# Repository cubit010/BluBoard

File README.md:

<h1 align="center">Bluboard</h1>

An nRF52840 dev board made to be embedded in a custom mechanical keyboard, with as many pins broken out as possible within JLCPCB's 6-layer specs.

---

## What is this?

BluBoard is a custom nRF52840 development board built for use inside a mechanical keyboard. The main goal was to break out as many GPIO pins as possible and also having proper RF capabilities 
most off-the-shelf options such as the nice nano is powerful, but comes at high cost while having low gpio count, this board tries to fix that.

---

## Form Factor

Slightly wider than a Raspberry Pi Pico. Uses two 1×20 pin headers, plus an extra two 1×3 headers near the usb c port for the pins that didn't fit in the main rows.

---

## Features

- **nRF52840** - ARM Cortex-M4F, BLE 5.x, 1MB flash, 256KB RAM
- **USB-C** - power and programming
- **BLE 5.x** - wireless support built in with trace antenna
- **SWD debug header** - for debugging
- **I2C** - broken out, available on most pins
- **SPI** - broken out, available on most pins
- **Analog IO** - most analog pins are broken out, on top or bottom layer with 1oz copper for signal
- **6-layer PCB** - JLCPCB, ENIG finish, filled via for bga
- **Built-in power management** - built in battery support through a jst-ph connector and a BQ24075 charger

---

## Pin Breakout

Power, ground, and GPIO are spread across both 1×20 headers. The extra 1×3 headers cover the remaining pins and utils such as swd.

> Full pinout table coming soon. Check the KiCad schematic in the meantime.

---

## Firmware

BluBoard targets **ZMK**, which has native nRF52840 support and works well for wireless keyboards. Bare metal / Nordic SDK also works if you need it.

> A ZMK shield definition for BluBoard is planned but not yet published.

---

## Why 6 layers?

Jlc's manufacturing options allow for cheap manufacturing of 6 layer boards, in addition, at this form factor, their 6 layer boards are cheaper than 4 layer, while having additional benefits such as enig finish, and free filled vias, so the bga solder points would not be a possible point of failure

---

## Previews
### Schematic

(don't ask why I did this)

### PCB
#### All

#### Top

#### In.1

#### In.2

#### In.3

#### In.4

#### Bottom

*Built with KiCad 9 and 10 · Fabricated via JLCPCB · Part of Hack Club [Blueprint](blueprint.hackclub.com) and [Stasis](stasis.hackclub.com)*

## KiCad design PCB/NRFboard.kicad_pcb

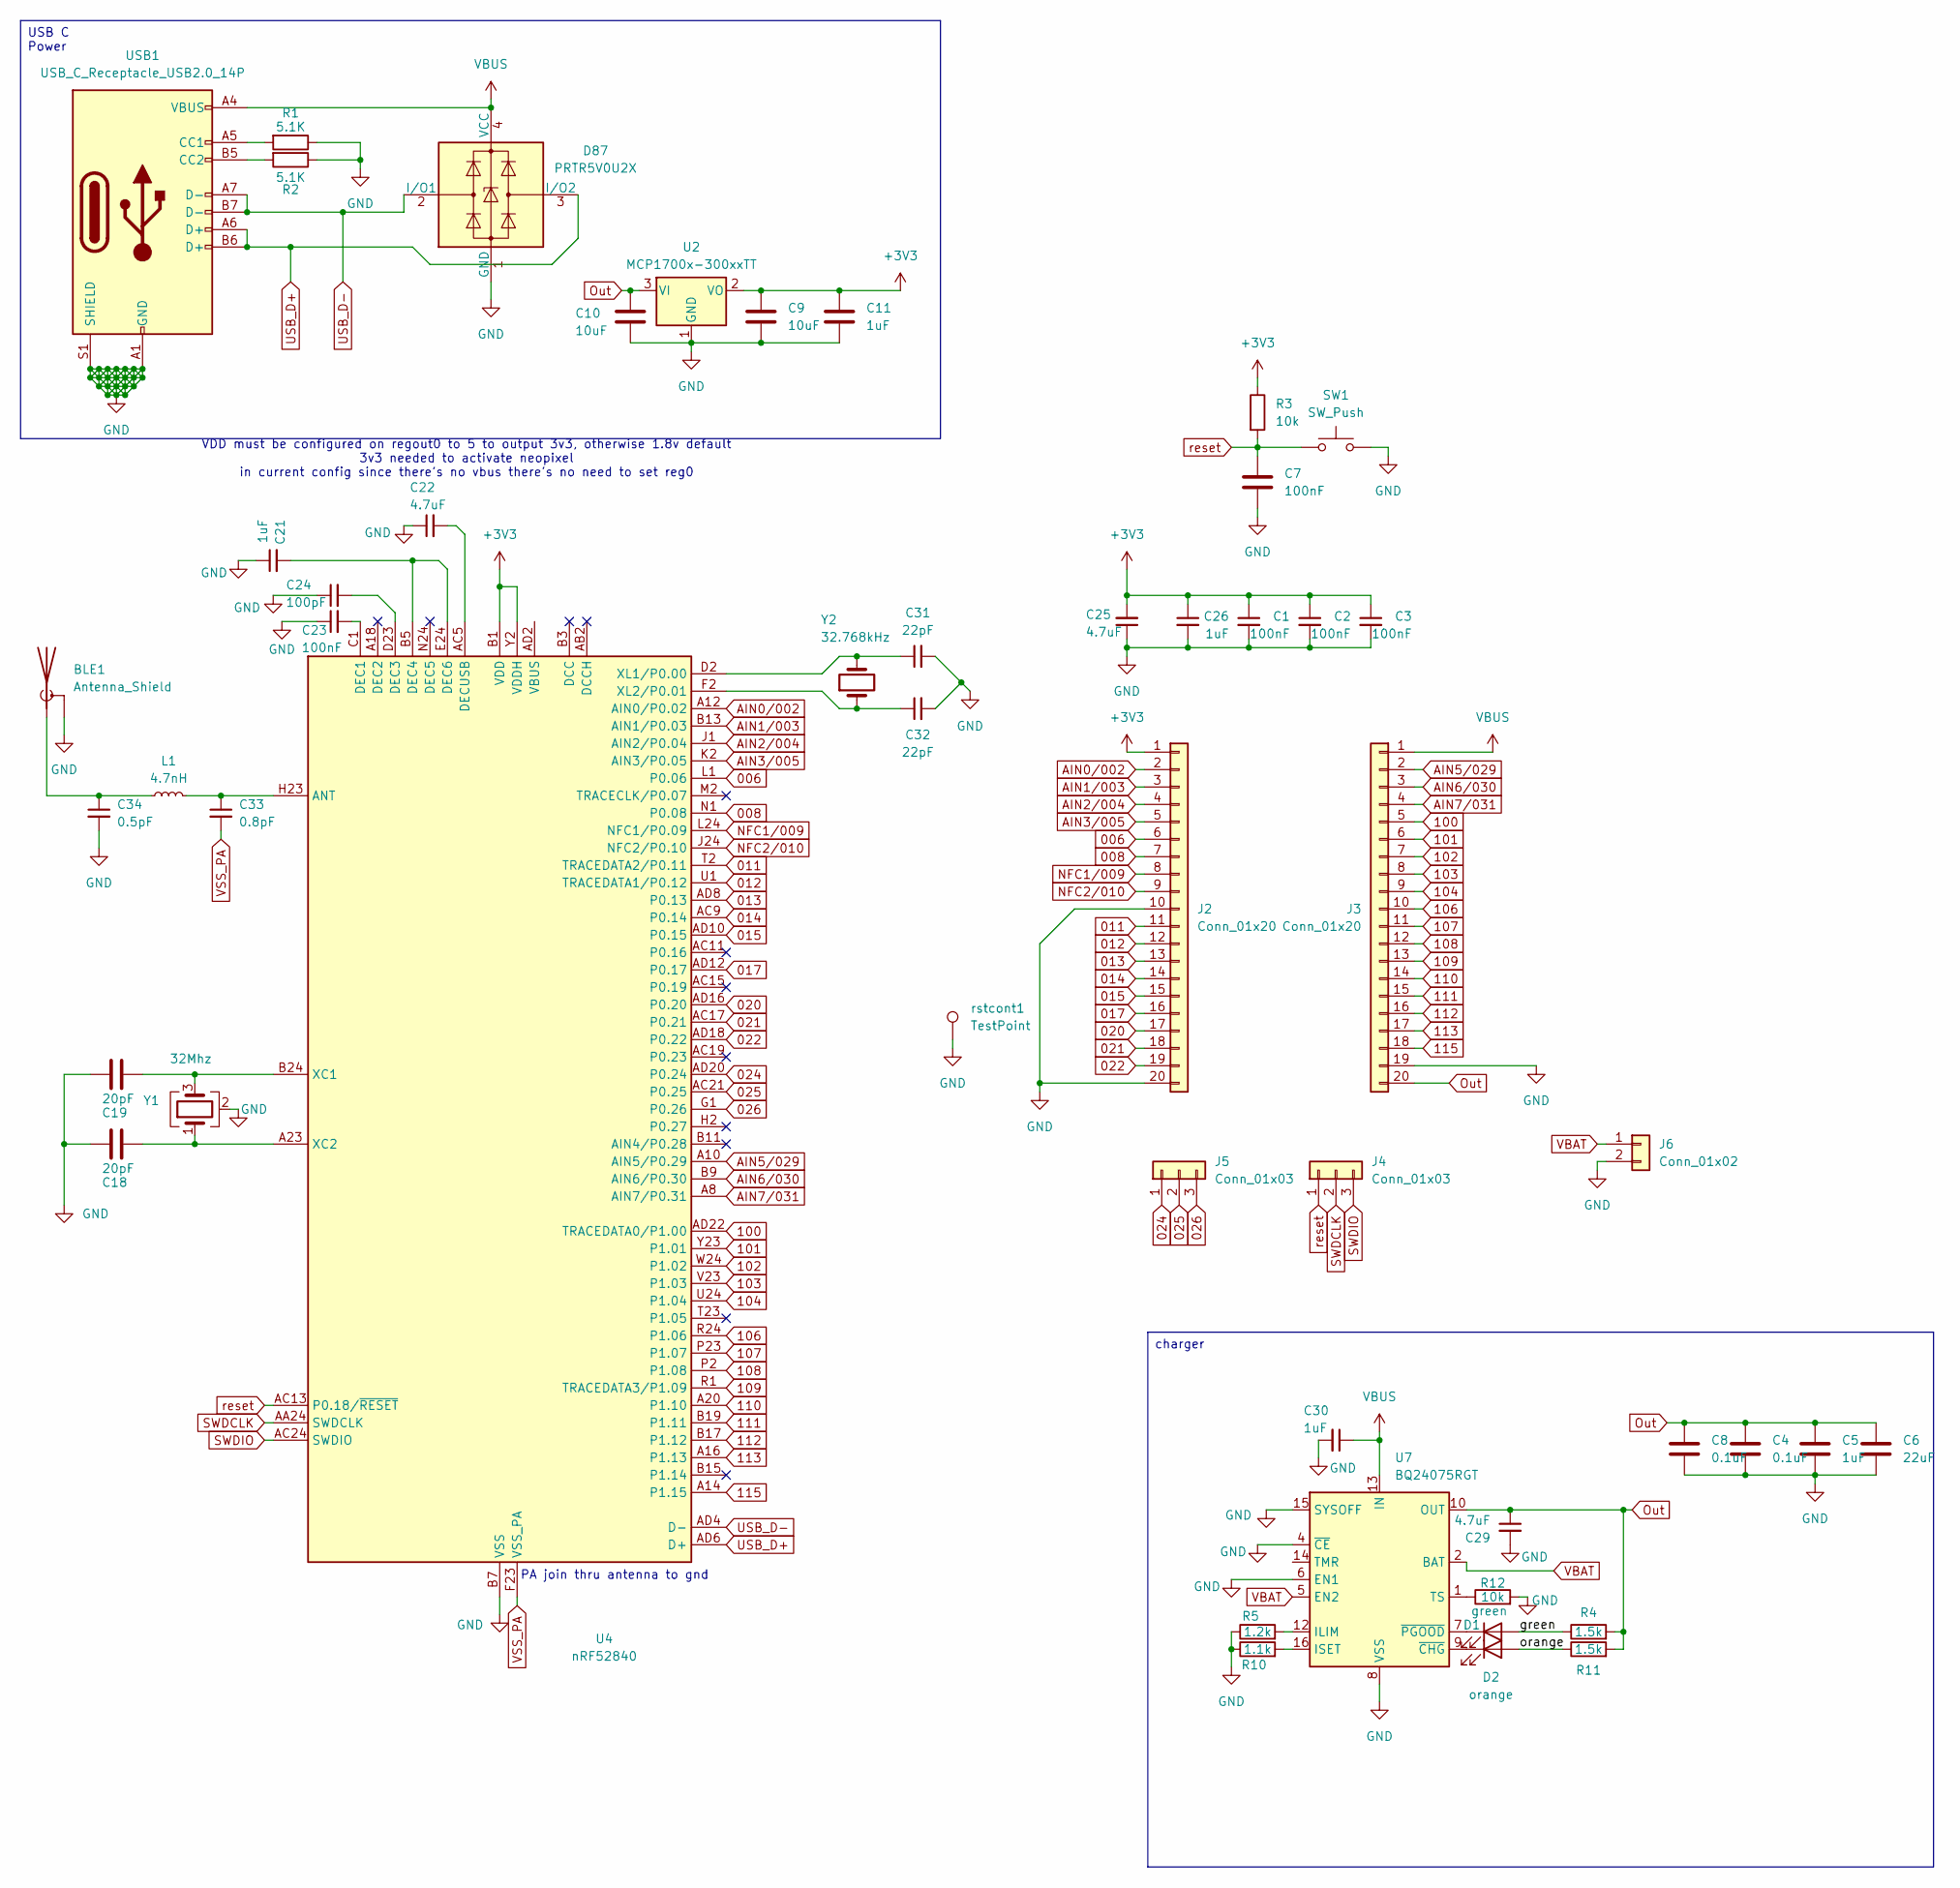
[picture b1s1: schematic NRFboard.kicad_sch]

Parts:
BLE1: Antenna_Shield; Texas_SWRA117D_2.4GHz_Right
C1, C2, C3, C7, C23: 100nF; C_0402_1005Metric
C4, C8: 0.1uF; C_0402_1005Metric
C5, C11, C21, C26, C30: 1uF; C_0402_1005Metric
C6: 22uF; C_0805_2012Metric
C9, C10: 10uF; C_0603_1608Metric
C18, C19: 20pF; C_0402_1005Metric
C22, C25, C29: 4.7uF; C_0603_1608Metric
C24: 100pF; C_0402_1005Metric
C31, C32: 22pF; C_0402_1005Metric
C33: 0.8pF; C_0402_1005Metric
C34: 0.5pF; C_0402_1005Metric
D1: green; LED_0805_2012Metric
D2: orange; LED_0805_2012Metric
D87: PRTR5V0U2X; SOT-143
J2, J3: Conn_01x20; PinHeader_1x20_P2.54mm_Vertical
J4, J5: Conn_01x03; PinHeader_1x03_P2.54mm_Vertical
J6: Conn_01x02; JST_PH_B2B-PH-K_1x02_P2.00mm_Vertical
L1: 4.7nH; L_0402_1005Metric
R1, R2: 5.1K; R_0402_1005Metric
R3, R12: 10k; R_0402_1005Metric
R4, R11: 1.5k; R_0402_1005Metric
R5: 1.2k; R_0402_1005Metric
R10: 1.1k; R_0402_1005Metric
SW1: SW_Push; SW_Push_SPST_NO_Alps_SKRK
U2: MCP1700x-300xxTT; SOT-23
U4: nRF52840; Nordic_AQFN-73-1EP_7x7mm_P0.5mm
U7: BQ24075RGT; VQFN-16-1EP_3x3mm_P0.5mm_EP1.6x1.6mm
USB1: USB_C_Receptacle_USB2.0_14P; USB_C_Receptacle_HRO_TYPE-C-31-M-12
Y1: 32Mhz; Crystal_SMD_3225-4Pin_3.2x2.5mm
Y2: 32.768kHz; Crystal_SMD_3215-2Pin_3.2x1.5mm
rstcont1: TestPoint; TestPoint_Pad_D1.0mm

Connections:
006: J2.6, U4.L1 (P0.06)
008: J2.7, U4.N1 (P0.08)
011: J2.11, U4.T2 (TRACEDATA2/P0.11)
012: J2.12, U4.U1 (TRACEDATA1/P0.12)
013: J2.13, U4.AD8 (P0.13)
014: J2.14, U4.AC9 (P0.14)
015: J2.15, U4.AD10 (P0.15)
017: J2.16, U4.AD12 (P0.17)
020: J2.17, U4.AD16 (P0.20)
021: J2.18, U4.AC17 (P0.21)
022: J2.19, U4.AD18 (P0.22)
024: J5.1, U4.AD20 (P0.24)
025: J5.2, U4.AC21 (P0.25)
026: J5.3, U4.G1 (P0.26)
100: J3.5, U4.AD22 (TRACEDATA0/P1.00)
101: J3.6, U4.Y23 (P1.01)
102: J3.7, U4.W24 (P1.02)
103: J3.8, U4.V23 (P1.03)
104: J3.9, U4.U24 (P1.04)
106: J3.10, U4.R24 (P1.06)
107: J3.11, U4.P23 (P1.07)
108: J3.12, U4.P2 (P1.08)
109: J3.13, U4.R1 (TRACEDATA3/P1.09)
110: J3.14, U4.A20 (P1.10)
111: J3.15, U4.B19 (P1.11)
112: J3.16, U4.B17 (P1.12)
113: J3.17, U4.A16 (P1.13)
115: J3.18, U4.A14 (P1.15)
+3V3: C1.1, C2.1, C3.1, C9.1, C11.1, C25.2, C26.1, J2.1, R3.1, U2.2 (VO), U4.A22 (VDD), U4.AD14 (VDD), U4.AD23 (VDD), U4.B1 (VDD), U4.W1 (VDD), U4.Y2 (VDDH)
/green: D1.2 (A), R4.1
/orange: D2.2 (A), R11.1
AIN0/002: J2.2, U4.A12 (AIN0/P0.02)
AIN1/003: J2.3, U4.B13 (AIN1/P0.03)
AIN2/004: J2.4, U4.J1 (AIN2/P0.04)
AIN3/005: J2.5, U4.K2 (AIN3/P0.05)
AIN5/029: J3.2, U4.A10 (AIN5/P0.29)
AIN6/030: J3.3, U4.B9 (AIN6/P0.30)
AIN7/031: J3.4, U4.A8 (AIN7/P0.31)
GND: BLE1.2 (Shield), C1.2, C2.2, C3.2, C4.2, C5.2, C6.2, C7.2, C8.2, C9.2, C10.1, C11.2, C18.1, C19.1, C21.1, C22.1, C23.1, C24.1, C25.1, C26.2, C29.2, C30.2, C31.2, C32.2, C34.2, D87.1 (GND), J2.10, J2.20, J3.19, J6.2, R1.1, R2.1, R5.1, R10.1, R12.2, SW1.2, U2.1 (GND), U4.B7 (VSS), U4.EP (VSS), U7.4 (~CE), U7.6 (EN1), U7.8 (VSS), U7.15 (SYSOFF), U7.17 (VSS), USB1.A1 (GND), USB1.A12 (GND), USB1.B1 (GND), USB1.B12 (GND), USB1.S1 (SHIELD), Y1.2 (G), Y1.4 (G), rstcont1.1 (1_1)
NFC1/009: J2.8, U4.L24 (NFC1/P0.09)
NFC2/010: J2.9, U4.J24 (NFC2/P0.10)
unnamed: BLE1.1 (A), C34.1, L1.1
unnamed: D1.1 (K), U7.7 (~PGOOD)
unnamed: D2.1 (K), U7.9 (~CHG)
unnamed: C33.1, L1.2, U4.H23 (ANT)
unnamed: C23.2, U4.C1 (DEC1)
unnamed: C24.2, U4.D23 (DEC3)
unnamed: C21.2, U4.B5 (DEC4), U4.E24 (DEC6)
unnamed: C22.2, U4.AC5 (DECUSB)
unnamed: C19.2, U4.B24 (XC1), Y1.3
unnamed: C18.2, U4.A23 (XC2), Y1.1
unnamed: C31.1, U4.D2 (XL1/P0.00), Y2.2
unnamed: C32.1, U4.F2 (XL2/P0.01), Y2.1
unnamed: R5.2, U7.12 (ILIM)
unnamed: R10.2, U7.16 (ISET)
unnamed: R12.1, U7.1 (TS)
unnamed: R1.2, USB1.A5 (CC1)
unnamed: R2.2, USB1.B5 (CC2)
Out: C4.1, C5.1, C6.1, C8.1, C10.2, C29.1, J3.20, R4.2, R11.2, U2.3 (VI), U7.10 (OUT), U7.11 (OUT)
SWDCLK: J4.2, U4.AA24 (SWDCLK)
SWDIO: J4.3, U4.AC24 (SWDIO)
USB_D+: D87.3 (I/O2), U4.AD6 (D+), USB1.A6 (D+), USB1.B6 (D+)
USB_D-: D87.2 (I/O1), U4.AD4 (D-), USB1.A7 (D-), USB1.B7 (D-)
VBAT: J6.1, U7.2 (BAT), U7.3 (BAT), U7.5 (EN2)
VBUS: C30.1, D87.4 (VCC), J3.1, U7.13 (IN), USB1.A4 (VBUS), USB1.A9 (VBUS), USB1.B4 (VBUS), USB1.B9 (VBUS)
VSS_PA: C33.2, U4.F23 (VSS_PA)
reset: C7.1, J4.1, R3.2, SW1.1, U4.AC13 (P0.18/~RESET)

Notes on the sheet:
VDD must be configured on regout0 to 5 to output 3v3, otherwise 1.8v default 3v3 needed to activate neopixel in current config since there's no vbus there's no need to set reg0
PA join thru antenna to gnd
charger
USB C Power

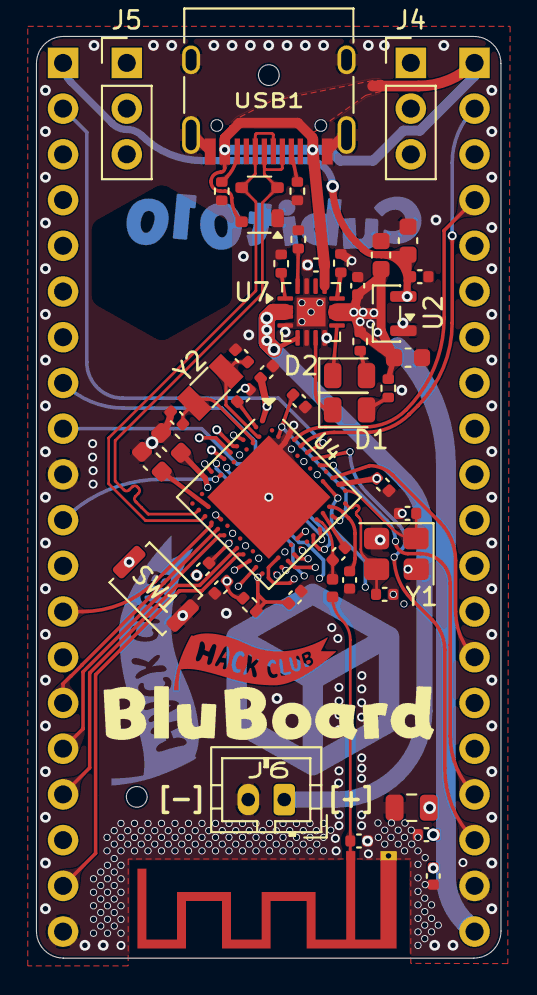
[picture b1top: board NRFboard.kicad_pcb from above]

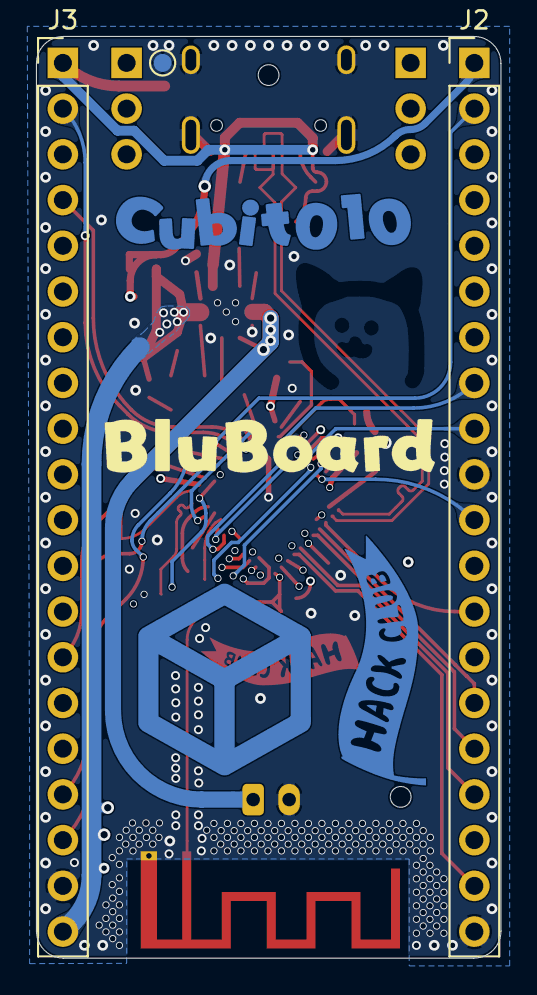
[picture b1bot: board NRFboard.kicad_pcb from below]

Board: 6 copper layers, 25.8 x 51.2 mm, 59 parts (8 on the bottom side), 67 nets.

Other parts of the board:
ToolHole1, ToolHole2: ToolingHole_1.152mm
car: car; carbig
cubit010lg: cubit010large
hackBack: hack
hacksm: hackSmall
logobig: logo; logoCU
logomid: logoCUmid

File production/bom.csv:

Designator,Footprint,Quantity,Value,LCSC Part #
AE1,Texas_SWRA117D_2.4GHz_Right,1,Antenna_Shield,
BLUTOOTH,blutoo,1,blutoo,
"C1, C2, C23, C3, C7",0402,5,100nF,
"C18, C19",0402,2,20pF,
"C21, C26, C30",0402,3,1uF,
"C22, C25, C29",0402,3,4.7uF,
C24,0402,1,100pF,
"C31, C32",0402,2,15pF,
C33,0402,1,0.8pF,
C34,0402,1,0.5pF,
CUBIT010,cubit010large,1,cubit010large,
D87,SOT-143,1,PRTR5V0U2X,
D89,0805,1,orange,
"HACKBACK, HACKFRONT",hack,2,hack,
J1,USB_C_Receptacle_HRO_TYPE-C-31-M-12,1,USB_C_Receptacle_USB2.0_14P,
"J2, J3",PinHeader_1x20_P2.54mm_Vertical,2,Conn_01x20,
"J4, J5",PinHeader_1x03_P2.54mm_Vertical,2,Conn_01x03,
L1,0402,1,4.7nH,
LOGO,Untitled,1,logo,
LOGOCULARGE,logoCUlarge,1,logoCUlarge,
LOGOSMALL,logoCUsmall,1,logoCUsmall,
"R1, R2",0402,2,5.1K,
R10,0402,1,2K,
"R11, R12, R3",0402,3,10k,
SW1,SW_Push_SPST_NO_Alps_SKRK,1,SW_Push,
U2,SOT-23,1,MCP1700x-300xxTT,
U4,Nordic_AQFN-73-1EP_7x7mm_P0.5mm,1,nRF52840,
U7,VQFN-16-1EP_3x3mm_P0.5mm_EP1.6x1.6mm,1,BQ24075RGT,
Y1,Crystal_SMD_3225-4Pin_3.2x2.5mm,1,32Mhz,
Y2,Crystal_SMD_3215-2Pin_3.2x1.5mm,1,32.768kHz,

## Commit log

2026-02-26 upload
2026-02-26 update folder struct + csv
2026-03-08 updated routing, should be finalized and ready for production
2026-03-22 update rf, wanted to add qspi but reverted
2026-03-25 updated layout, added more vias, matched impedance for usb line for a coplanar diff
2026-04-18 Add README for BluBoard development board
    Added detailed information about the BluBoard, including features, form factor, pin breakout, firmware, and manufacturing details.
2026-04-18 clean up readme
2026-04-18 small note
2026-04-18 Update README with power management details
    Added information about built-in power management and battery support.
2026-04-18 Add new banner image to README
    Updated README to include a new image for BluBoard.
2026-04-18 Update README header and formatting
